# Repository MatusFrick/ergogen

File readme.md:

# Ergogen

This is my fork of [Ergogen](https://github.com/ergogen/ergogen).

Ergogen is a keyboard generator that aims to provide a common configuration format to describe **ergonomic** 2D layouts, and generate automatic plates, cases, and (un-routed) PCBs for them.
The project grew out of (and is an integral part of) the [Absolem keyboard](https://zealot.hu/absolem), and shares its [Discord server](https://discord.gg/nbKcAZB) as well.

For usage and config information, please refer to the [docs](https://docs.ergogen.xyz).

## Usage

I use some components from Ben Vallack [Ergogen Fork](https://github.com/benvallack/ergogen). Use this app with [development usage](https://docs.ergogen.xyz/#development-usage) because of these components.

You can find my config in [lebeda.yaml](lebeda.yaml)

## Contributions

Feature ideas, documentation improvements, examples, tests, or pull requests welcome!
Get in touch [on Discord](https://discord.gg/nbKcAZB), and we can definitely find something you can help with, if you'd like to.

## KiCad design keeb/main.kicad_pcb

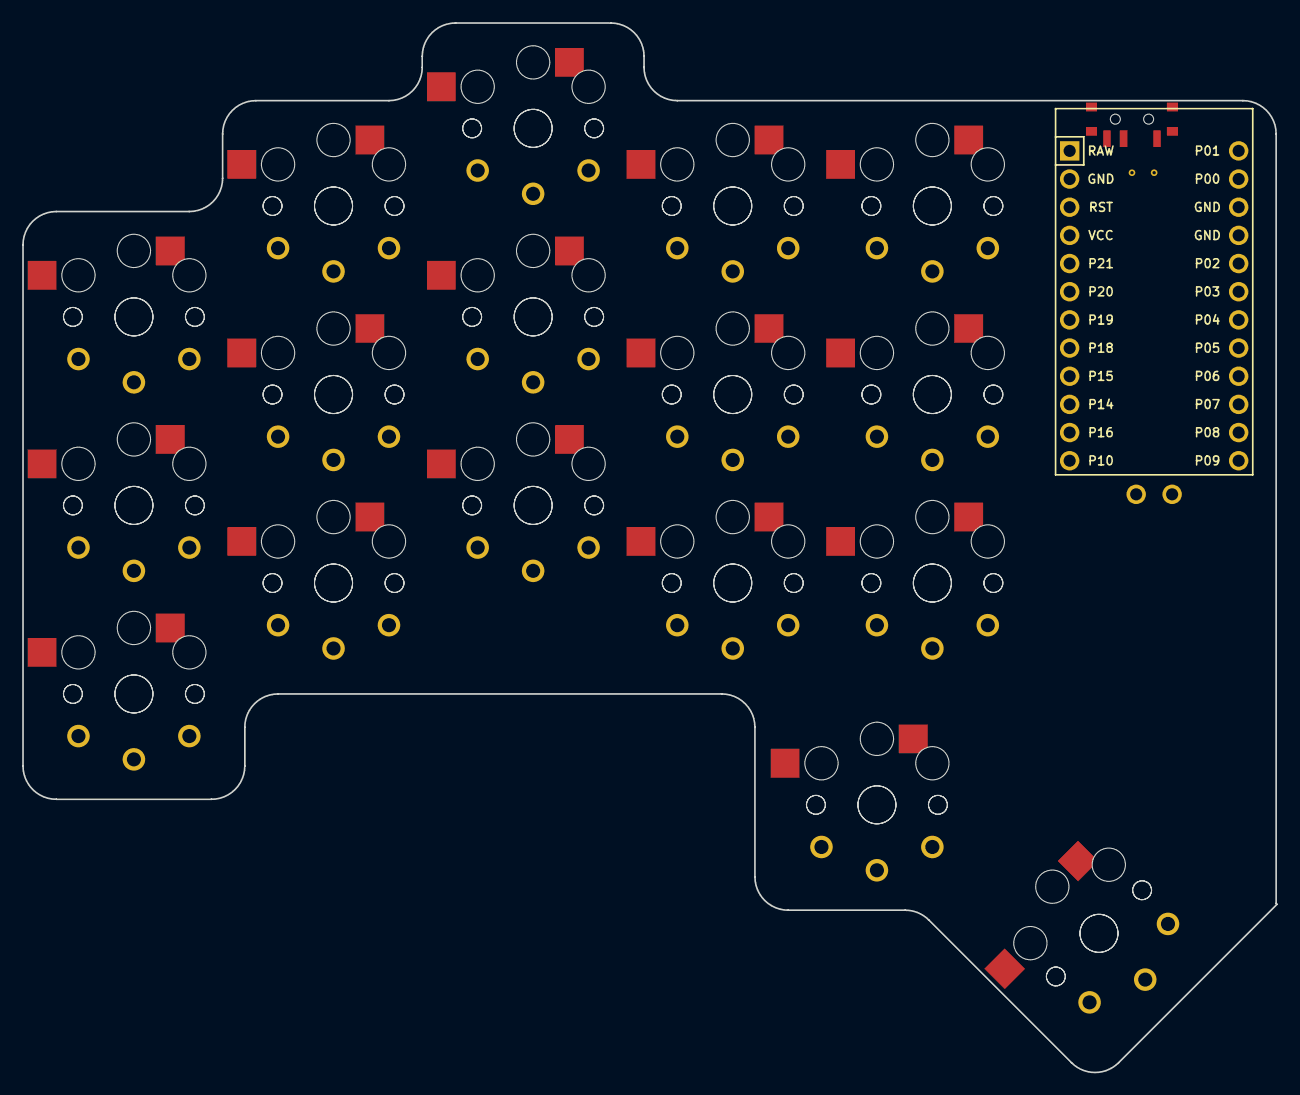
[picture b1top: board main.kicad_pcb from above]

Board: 2 copper layers, 113.1 x 94.6 mm, 35 parts (0 on the bottom side), 18 nets, no tracks yet.

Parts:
MCU1: ProMicro
S1, S2, S3, S4, S5, S6, S7, S8, S9, S10, S11, S12, S13, S14, S15, S16, S17, S18, S19, S20, S21, S22, S23, S24, S25, S26, S27, S28, S29, S30, S31, S32, S33, S34: PG1350

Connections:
GND: MCU1.2, MCU1.15, MCU1.16, S1.2, S2.2, S3.2, S4.2, S5.2, S6.2, S7.2, S8.2, S9.2, S10.2, S11.2, S12.2, S13.2, S14.2, S15.2, S16.2, S17.2, S18.2, S19.2, S20.2, S21.2, S22.2, S23.2, S24.2, S25.2, S26.2, S27.2, S28.2, S29.2, S30.2, S31.2, S32.2, S33.2, S34.2
P0: MCU1.14, S9.1, S10.1
P2: MCU1.17, S3.1, S4.1
P3: MCU1.18, S1.1, S2.1
P4: MCU1.19, S7.1, S8.1
P5: MCU1.20, S13.1, S14.1
P6: MCU1.21, S19.1, S20.1
P7: MCU1.22, S25.1, S26.1
P8: MCU1.23, S31.1, S32.1
P9: MCU1.24, S33.1, S34.1
P10: MCU1.12, S21.1, S22.1
P14: MCU1.10, S15.1, S16.1
P15: MCU1.9, S5.1, S6.1
P16: MCU1.11, S27.1, S28.1
P18: MCU1.8, S11.1, S12.1
P19: MCU1.7, S17.1, S18.1
P20: MCU1.6, S23.1, S24.1
P21: MCU1.5, S29.1, S30.1

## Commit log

2022-03-20 First PCB
2022-03-30 Gitignore fix
